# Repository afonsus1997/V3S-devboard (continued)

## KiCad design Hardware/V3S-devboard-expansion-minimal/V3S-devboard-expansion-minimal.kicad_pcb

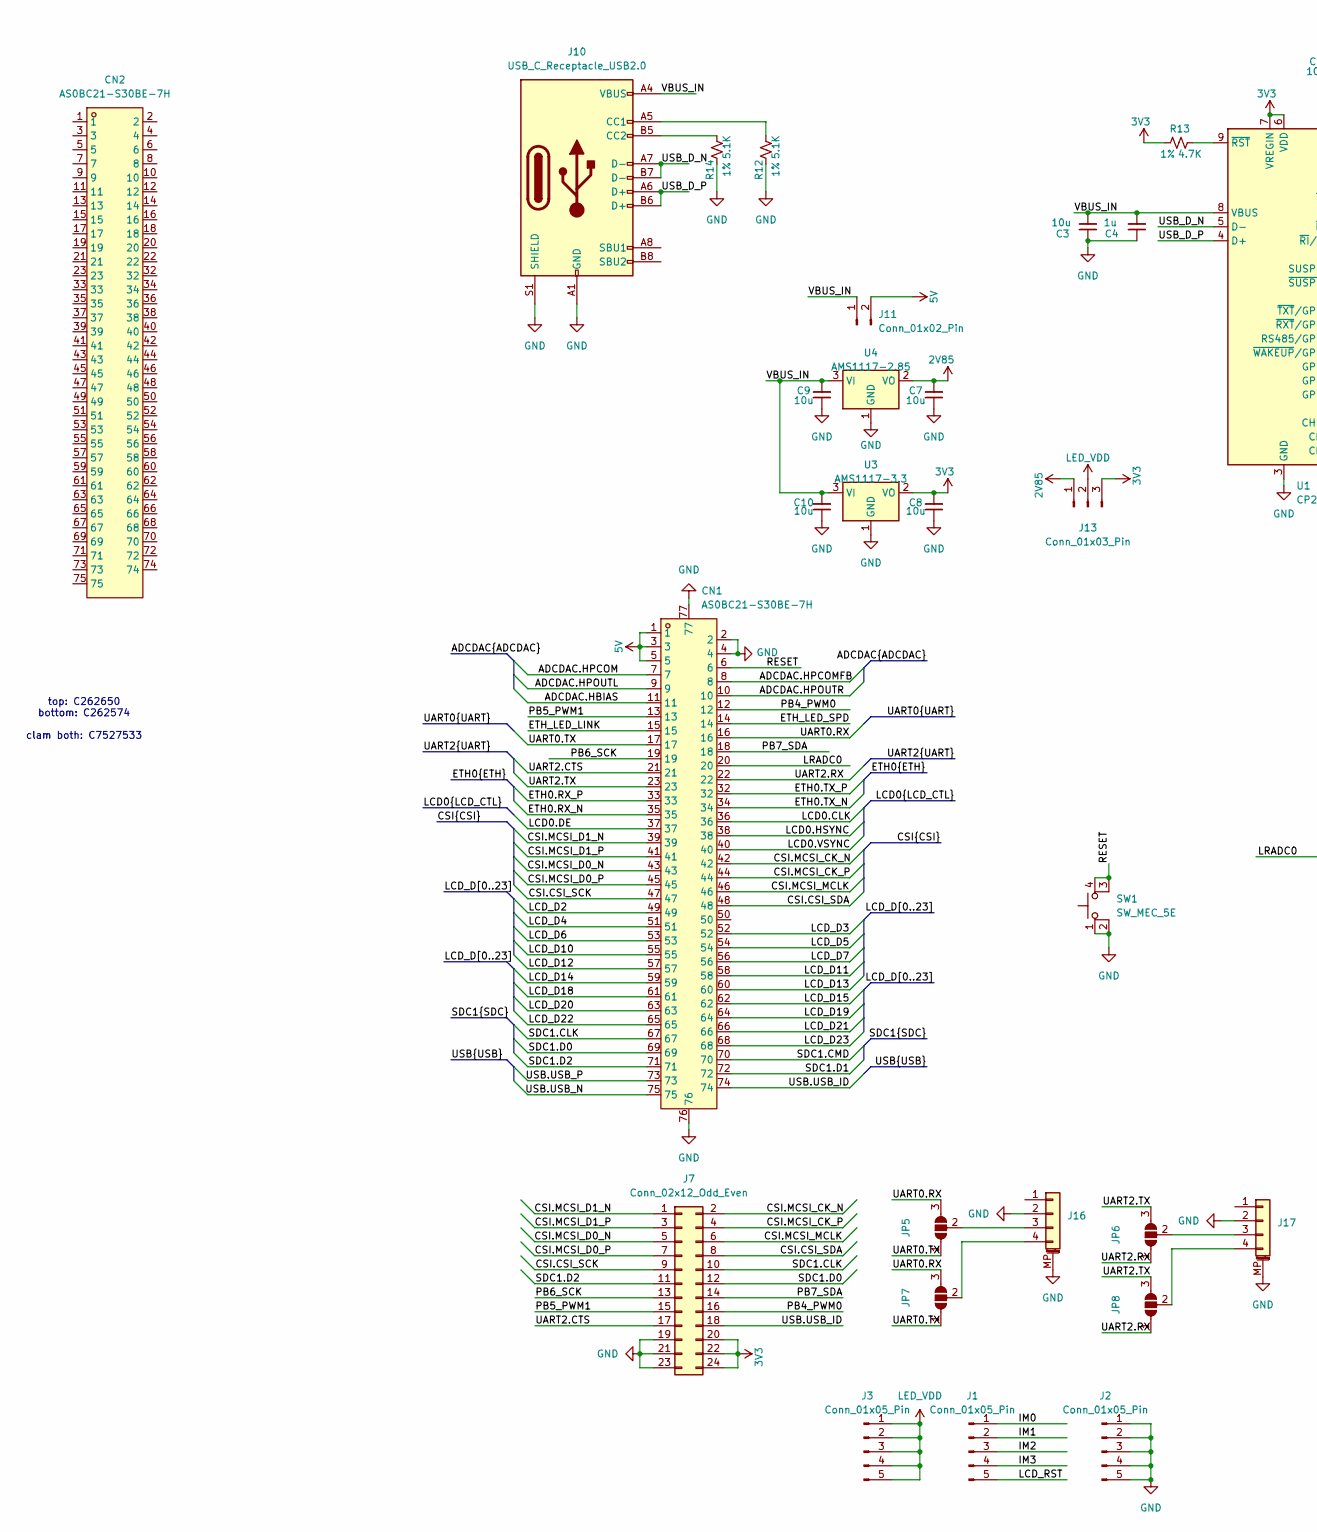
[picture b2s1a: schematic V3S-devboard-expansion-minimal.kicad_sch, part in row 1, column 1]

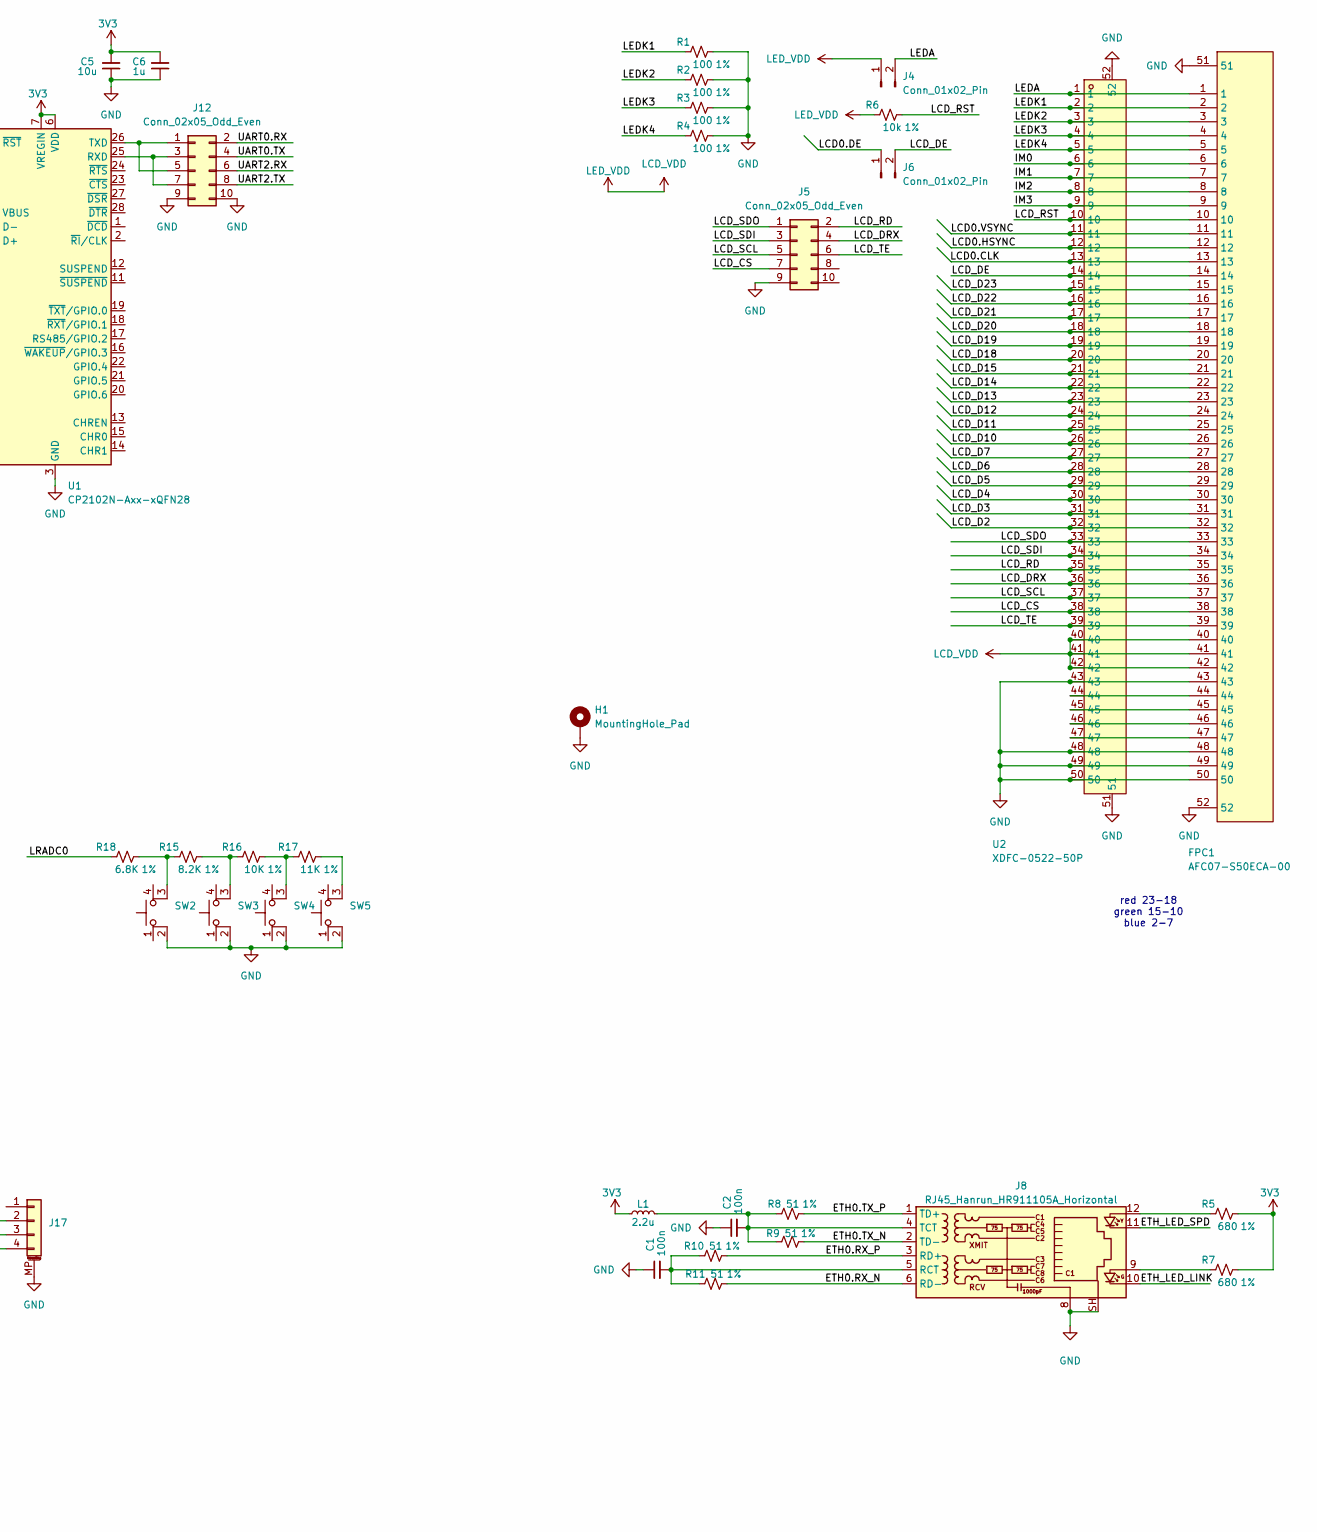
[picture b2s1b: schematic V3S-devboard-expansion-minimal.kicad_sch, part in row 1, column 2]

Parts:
C1, C2: 100n; C_0603_1608Metric; LCSC C1525
C3, C5, C7, C8, C9, C10: 10u; C_0603_1608Metric; LCSC C1525
C4, C6: 1u; C_0603_1608Metric; LCSC C1525
CN1: AS0BC21-S30BE-7H; CONN-SMD_AS0BC21-S30BE-7H; LCSC Part C3020019
CN2: AS0BC21-S30BE-7H; m2-padKeyE; LCSC Part C3020019
FPC1: AFC07-S50ECA-00; FPC-SMD_AFC07-S50ECA-00; LCSC C262650
H1: MountingHole_Pad; screwnut; LCSC C2928188
J1, J2, J3: Conn_01x05_Pin; PinHeader_1x05_P2.54mm_Vertical
J4, J6, J11: Conn_01x02_Pin; PinHeader_1x02_P2.54mm_Vertical
J5: Conn_02x05_Odd_Even; PinHeader_2x05_P2.54mm_Vertical
J7: Conn_02x12_Odd_Even; PinSocket_2x12_P2.54mm_Vertical; LCSC C2685134
J8: RJ45_Hanrun_HR911105A_Horizontal; LCSC C12074
J10: USB_C_Receptacle_USB2.0; USB_C_Receptacle_HCTL_HC-TYPE-C-16P-01A; LCSC C2894897
J12: Conn_02x05_Odd_Even; PinHeader_2x05_P2.54mm_Vertical_SMD
J13: Conn_01x03_Pin; PinSocket_1x03_P2.54mm_Vertical
J16, J17: Conn_01x04_MountingPin; CONN-SMD_HCZZ0021-4; LCSC C7433709
JP5, JP6, JP7, JP8: SolderJumper_3_Open; SolderJumper-3_P1.3mm_Open_RoundedPad1.0x1.5mm_NumberLabels
L1: 2.2u; L_1008_2520Metric; LCSC C86092
R1, R2, R3, R4: 100; R_0603_1608Metric; LCSC C60491
R5, R7: 680; R_0603_1608Metric; LCSC C60491
R6: 10k; R_0402_1005Metric; LCSC C60491
R8, R9, R10, R11: 51; R_0603_1608Metric; LCSC C60491
R12, R14: 5.1K; R_0603_1608Metric; LCSC C60491
R13: 4.7K; R_0603_1608Metric; LCSC C60491
R15: 8.2K; R_0603_1608Metric; LCSC C25981
R16: 10K; R_0603_1608Metric; LCSC C25804
R17: 11K; R_0603_1608Metric; LCSC C103227
R18: 6.8K; R_0603_1608Metric; LCSC C23212
SW1, SW2, SW3, SW4, SW5: SW_MEC_5E; SW_SKRPACE010; LCSC C139797
U1: CP2102N-Axx-xQFN28; QFN-28-1EP_5x5mm_P0.5mm_EP3.1x3.1mm; LCSC C964632
U2: XDFC-0522-50P; FPC-SMD_50P-P0.50_LX_XDFC-0522-50P; LCSC Part C7527533
U3: AMS1117-3.3; SOT-223-3_TabPin2; LCSC C426566
U4: AMS1117-2.85; SOT-223-3_TabPin2; LCSC C14791

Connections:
2V85: C7.2, J13.1, U4.2 (VO)
3V3: C5.2, C6.2, C8.2, J7.20, J7.22, J7.24, J13.3, L1.1, R5.2, R7.2, R13.2, U1.6 (VDD), U1.7 (VREGIN), U3.2 (VO)
5V: CN1.1, CN1.3, CN1.5, J11.2
/ADCDAC.HBIAS: CN1.11
/ADCDAC.HPCOM: CN1.7
/ADCDAC.HPCOMFB: CN1.8
/ADCDAC.HPOUTL: CN1.9
/ADCDAC.HPOUTR: CN1.10
/CSI.CSI_SCK: CN1.47, J7.9
/CSI.CSI_SDA: CN1.48, J7.8
/CSI.MCSI_CK_N: CN1.42, J7.2
/CSI.MCSI_CK_P: CN1.44, J7.4
/CSI.MCSI_D0_N: CN1.43, J7.5
/CSI.MCSI_D0_P: CN1.45, J7.7
/CSI.MCSI_D1_N: CN1.39, J7.1
/CSI.MCSI_D1_P: CN1.41, J7.3
/CSI.MCSI_MCLK: CN1.46, J7.6
/ETH0.RX_N: CN1.35, J8.6 (RD-), R11.2
/ETH0.RX_P: CN1.33, J8.3 (RD+), R10.2
/ETH0.TX_N: CN1.34, J8.2 (TD-), R9.2
/ETH0.TX_P: CN1.32, J8.1 (TD+), R8.2
/ETH_LED_LINK: CN1.15, J8.10
/ETH_LED_SPD: CN1.14, J8.11
/IM0: FPC1.6, J1.1, U2.6
/IM1: FPC1.7, J1.2, U2.7
/IM2: FPC1.8, J1.3, U2.8
/IM3: FPC1.9, J1.4, U2.9
/LCD0.CLK: CN1.36, FPC1.13, U2.13
/LCD0.DE: CN1.37, J6.1
/LCD0.HSYNC: CN1.38, FPC1.12, U2.12
/LCD0.VSYNC: CN1.40, FPC1.11, U2.11
/LCD_CS: FPC1.38, J5.7, U2.38
/LCD_D2: CN1.49, FPC1.32, U2.32
/LCD_D3: CN1.52, FPC1.31, U2.31
/LCD_D4: CN1.51, FPC1.30, U2.30
/LCD_D5: CN1.54, FPC1.29, U2.29
/LCD_D6: CN1.53, FPC1.28, U2.28
/LCD_D7: CN1.56, FPC1.27, U2.27
/LCD_D10: CN1.55, FPC1.26, U2.26
/LCD_D11: CN1.58, FPC1.25, U2.25
/LCD_D12: CN1.57, FPC1.24, U2.24
/LCD_D13: CN1.60, FPC1.23, U2.23
/LCD_D14: CN1.59, FPC1.22, U2.22
/LCD_D15: CN1.62, FPC1.21, U2.21
/LCD_D18: CN1.61, FPC1.20, U2.20
/LCD_D19: CN1.64, FPC1.19, U2.19
/LCD_D20: CN1.63, FPC1.18, U2.18
/LCD_D21: CN1.66, FPC1.17, U2.17
/LCD_D22: CN1.65, FPC1.16, U2.16
/LCD_D23: CN1.68, FPC1.15, U2.15
/LCD_DE: FPC1.14, J6.2, U2.14
/LCD_DRX: FPC1.36, J5.4, U2.36
/LCD_RD: FPC1.35, J5.2, U2.35
/LCD_RST: FPC1.10, J1.5, R6.2, U2.10
/LCD_SCL: FPC1.37, J5.5, U2.37
/LCD_SDI: FPC1.34, J5.3, U2.34
/LCD_SDO: FPC1.33, J5.1, U2.33
/LCD_TE: FPC1.39, J5.6, U2.39
/LEDA: FPC1.1, J4.2, U2.1
/LEDK1: FPC1.2, R1.1, U2.2
/LEDK2: FPC1.3, R2.1, U2.3
/LEDK3: FPC1.4, R3.1, U2.4
/LEDK4: FPC1.5, R4.1, U2.5
/LRADC0: CN1.20, R18.1
/PB4_PWM0: CN1.12, J7.16
/PB5_PWM1: CN1.13, J7.15
/PB6_SCK: CN1.19, J7.13
/PB7_SDA: CN1.18, J7.14
/RESET: CN1.6, SW1.3 (K), SW1.4 (A)
/SDC1.CLK: CN1.67, J7.10
/SDC1.CMD: CN1.70
/SDC1.D0: CN1.69, J7.12
/SDC1.D1: CN1.72
/SDC1.D2: CN1.71, J7.11
/UART0.RX: CN1.16, J12.2, JP5.3 (B), JP7.3 (B)
/UART0.TX: CN1.17, J12.4, JP5.1 (A), JP7.1 (A)
/UART2.CTS: CN1.21, J7.17
/UART2.RX: CN1.22, J12.6, JP6.1 (A), JP8.1 (A)
/UART2.TX: CN1.23, J12.8, JP6.3 (B), JP8.3 (B)
/USB.USB_ID: CN1.74, J7.18
/USB.USB_N: CN1.75
/USB.USB_P: CN1.73
/USB_D_N: J10.A7 (D-), J10.B7 (D-), U1.5 (D-)
/USB_D_P: J10.A6 (D+), J10.B6 (D+), U1.4 (D+)
/VBUS_IN: C3.2, C4.2, C9.2, C10.2, J10.A4 (VBUS), J10.A9 (VBUS), J10.B4 (VBUS), J10.B9 (VBUS), J11.1, U1.8 (VBUS), U3.3 (VI), U4.3 (VI)
GND: C1.1, C2.1, C3.1, C4.1, C5.1, C6.1, C7.1, C8.1, C9.1, C10.1, CN1.2, CN1.4, CN1.76, CN1.77, FPC1.43, FPC1.48, FPC1.49, FPC1.50, FPC1.51, FPC1.52, H1.1, J2.1, J2.2, J2.3, J2.4, J2.5, J5.9, J7.19, J7.21, J7.23, J8.8, J8.SH, J10.A1 (GND), J10.A12 (GND), J10.B1 (GND), J10.B12 (GND), J10.S1 (SHIELD), J12.9, J12.10, J16.2, J16.MP (MountPin), J17.2, J17.MP (MountPin), R1.2, R2.2, R3.2, R4.2, R12.2, R14.2, SW1.1, SW1.2, SW2.2, SW3.2, SW4.2, SW5.2, U1.3 (GND), U1.29 (GND), U2.43, U2.48, U2.49, U2.50, U2.51, U2.52, U3.1 (GND), U4.1 (GND)
LCD_VDD: FPC1.40, FPC1.41, FPC1.42, J3.1, J3.2, J3.3, J3.4, J3.5, J4.1, J13.2, R6.1, U2.40, U2.41, U2.42
unnamed: FPC1.44, U2.44
unnamed: FPC1.45, U2.45
unnamed: FPC1.46, U2.46
unnamed: FPC1.47, U2.47
unnamed: J8.9, R7.1
unnamed: J8.12, R5.1
unnamed: C1.2, J8.5 (RCT), R10.1, R11.1
unnamed: C2.2, J8.4 (TCT), L1.2, R8.1, R9.1
unnamed: J10.A5 (CC1), R12.1
unnamed: J10.B5 (CC2), R14.1
unnamed: J12.1, J12.5, U1.26 (TXD)
unnamed: J12.3, J12.7, U1.25 (RXD)
unnamed: J16.3, JP5.2 (C)
unnamed: J16.4, JP7.2 (C)
unnamed: J17.3, JP6.2 (C)
unnamed: J17.4, JP8.2 (C)
unnamed: R15.1, R18.2, SW2.3 (K)
unnamed: R15.2, R16.1, SW3.3 (K)
unnamed: R16.2, R17.1, SW4.3 (K)
unnamed: R17.2, SW5.3 (K)
unnamed: R13.1, U1.9 (~RST)

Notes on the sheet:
red 23-18 green 15-10 blue 2-7
top: C262650 bottom: C262574 clam both: C7527533

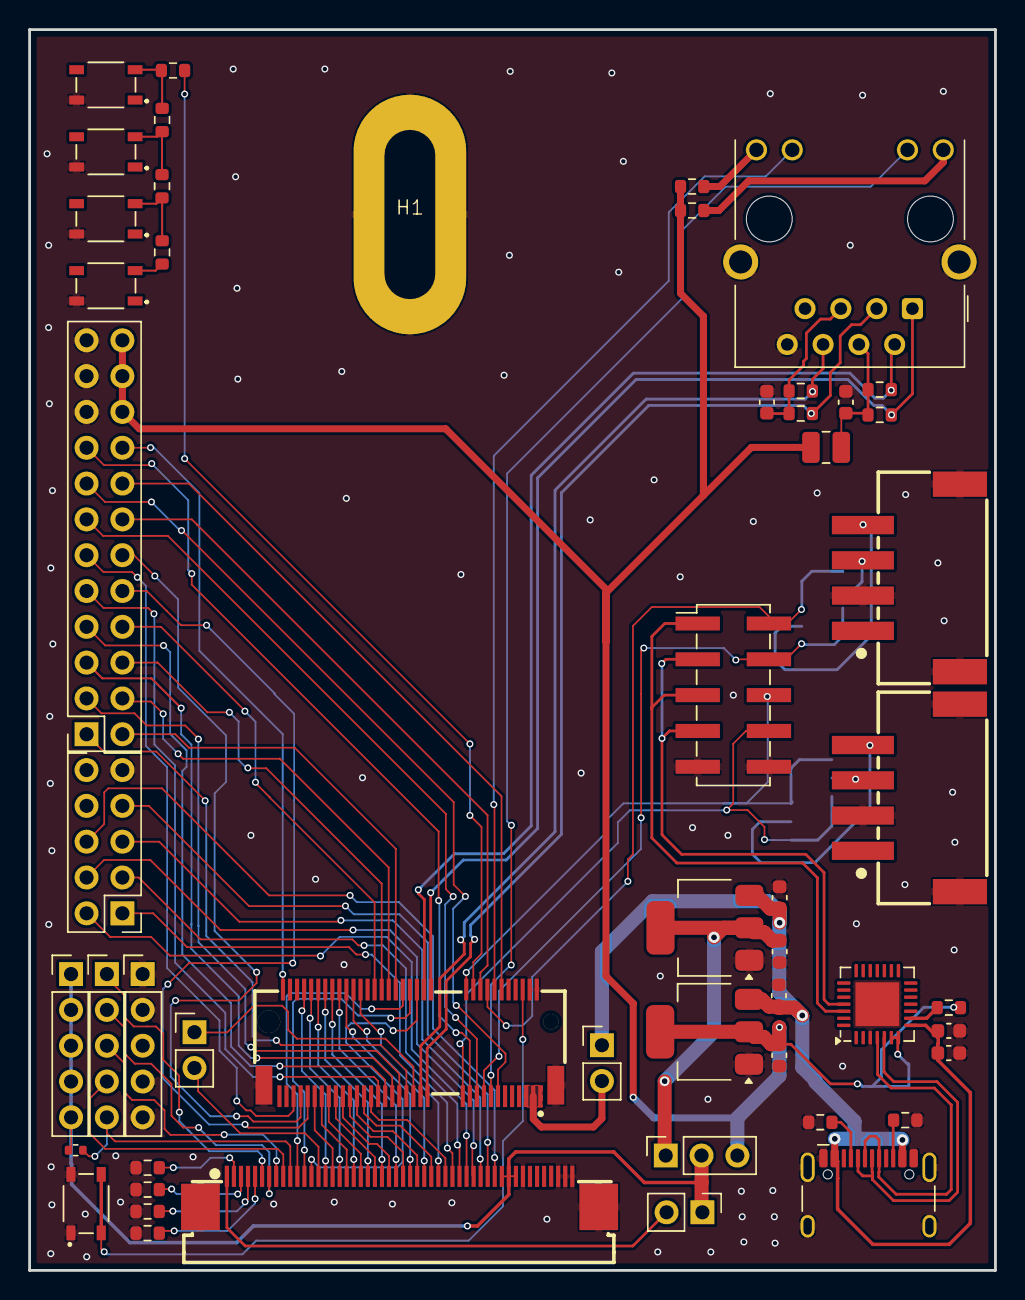
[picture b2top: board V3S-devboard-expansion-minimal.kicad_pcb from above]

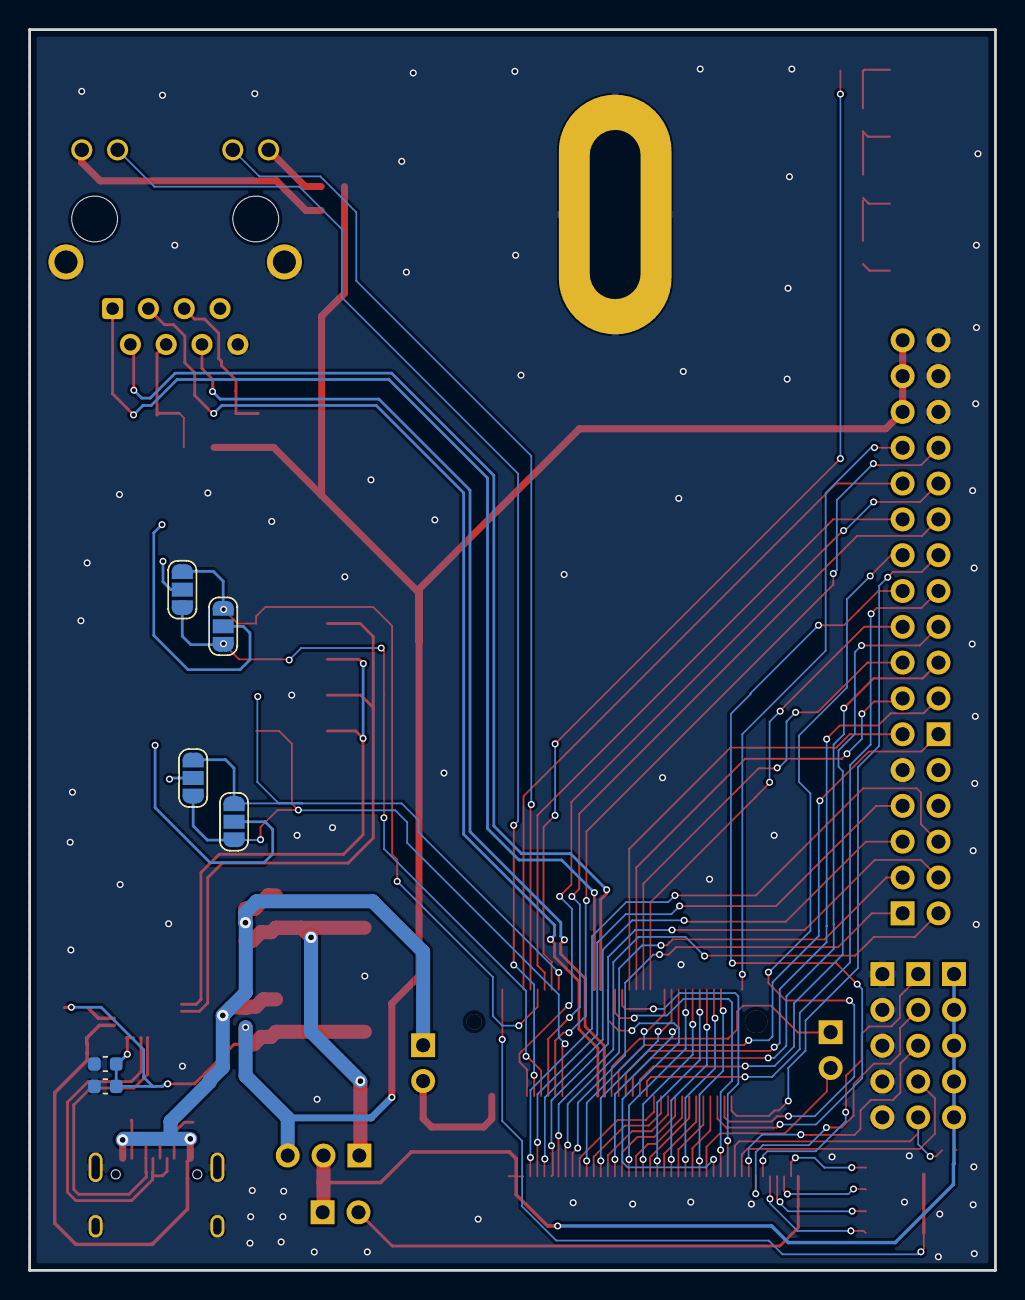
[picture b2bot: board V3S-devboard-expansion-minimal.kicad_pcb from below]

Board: 2 copper layers, 68.5 x 88.0 mm, 58 parts (6 on the bottom side), 95 nets.

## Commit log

2024-03-03 Started working in schematic
2024-03-07 minor changes
2024-03-07 more shcematic
2024-03-07 more schematic changes
2024-03-12 schematic work
2024-03-13 small improvements
2024-03-13 added some power connections
2024-03-22 schematic improvements
2024-03-23 Removed old project. Schematic improvements
2024-03-26 general improvements. power almost complete
2024-03-26 new power designators
2024-03-26 CPU schematic improvements
2024-03-26 minor improvements and fixes
2024-03-27 fixed minor schematic issues
2024-03-27 started preparing layout
2024-03-27 layout improvements.
2024-03-28 some layout
2024-03-29 layout testing
2024-03-29 more layout testing
2024-04-02 small layout
2024-04-03 more tests
2024-04-04 more layout
2024-04-05 layout
2024-04-06 re-annotated everything
2024-04-07 pre production tests
2024-04-07 minor fixes
2024-04-07 started working on exp board
2024-04-08 expansion board work
2024-04-10 expansion layout and schematic
2024-04-10 expansion board layout
2024-04-11 working on final touches
2024-04-11 Minor changes. Sent to fab
2024-04-12 fixed clearance problems, sent to fab
2024-04-12 changed clearances for devboard, sent to fab
2024-04-12 sent to fab... again
2024-04-12 Minor changed. Final version sent to fab (really)
2024-04-30 wrong order of pins of regulator
2024-06-13 added buildroot and gitignore
2024-06-14 Started adding OS development environment
